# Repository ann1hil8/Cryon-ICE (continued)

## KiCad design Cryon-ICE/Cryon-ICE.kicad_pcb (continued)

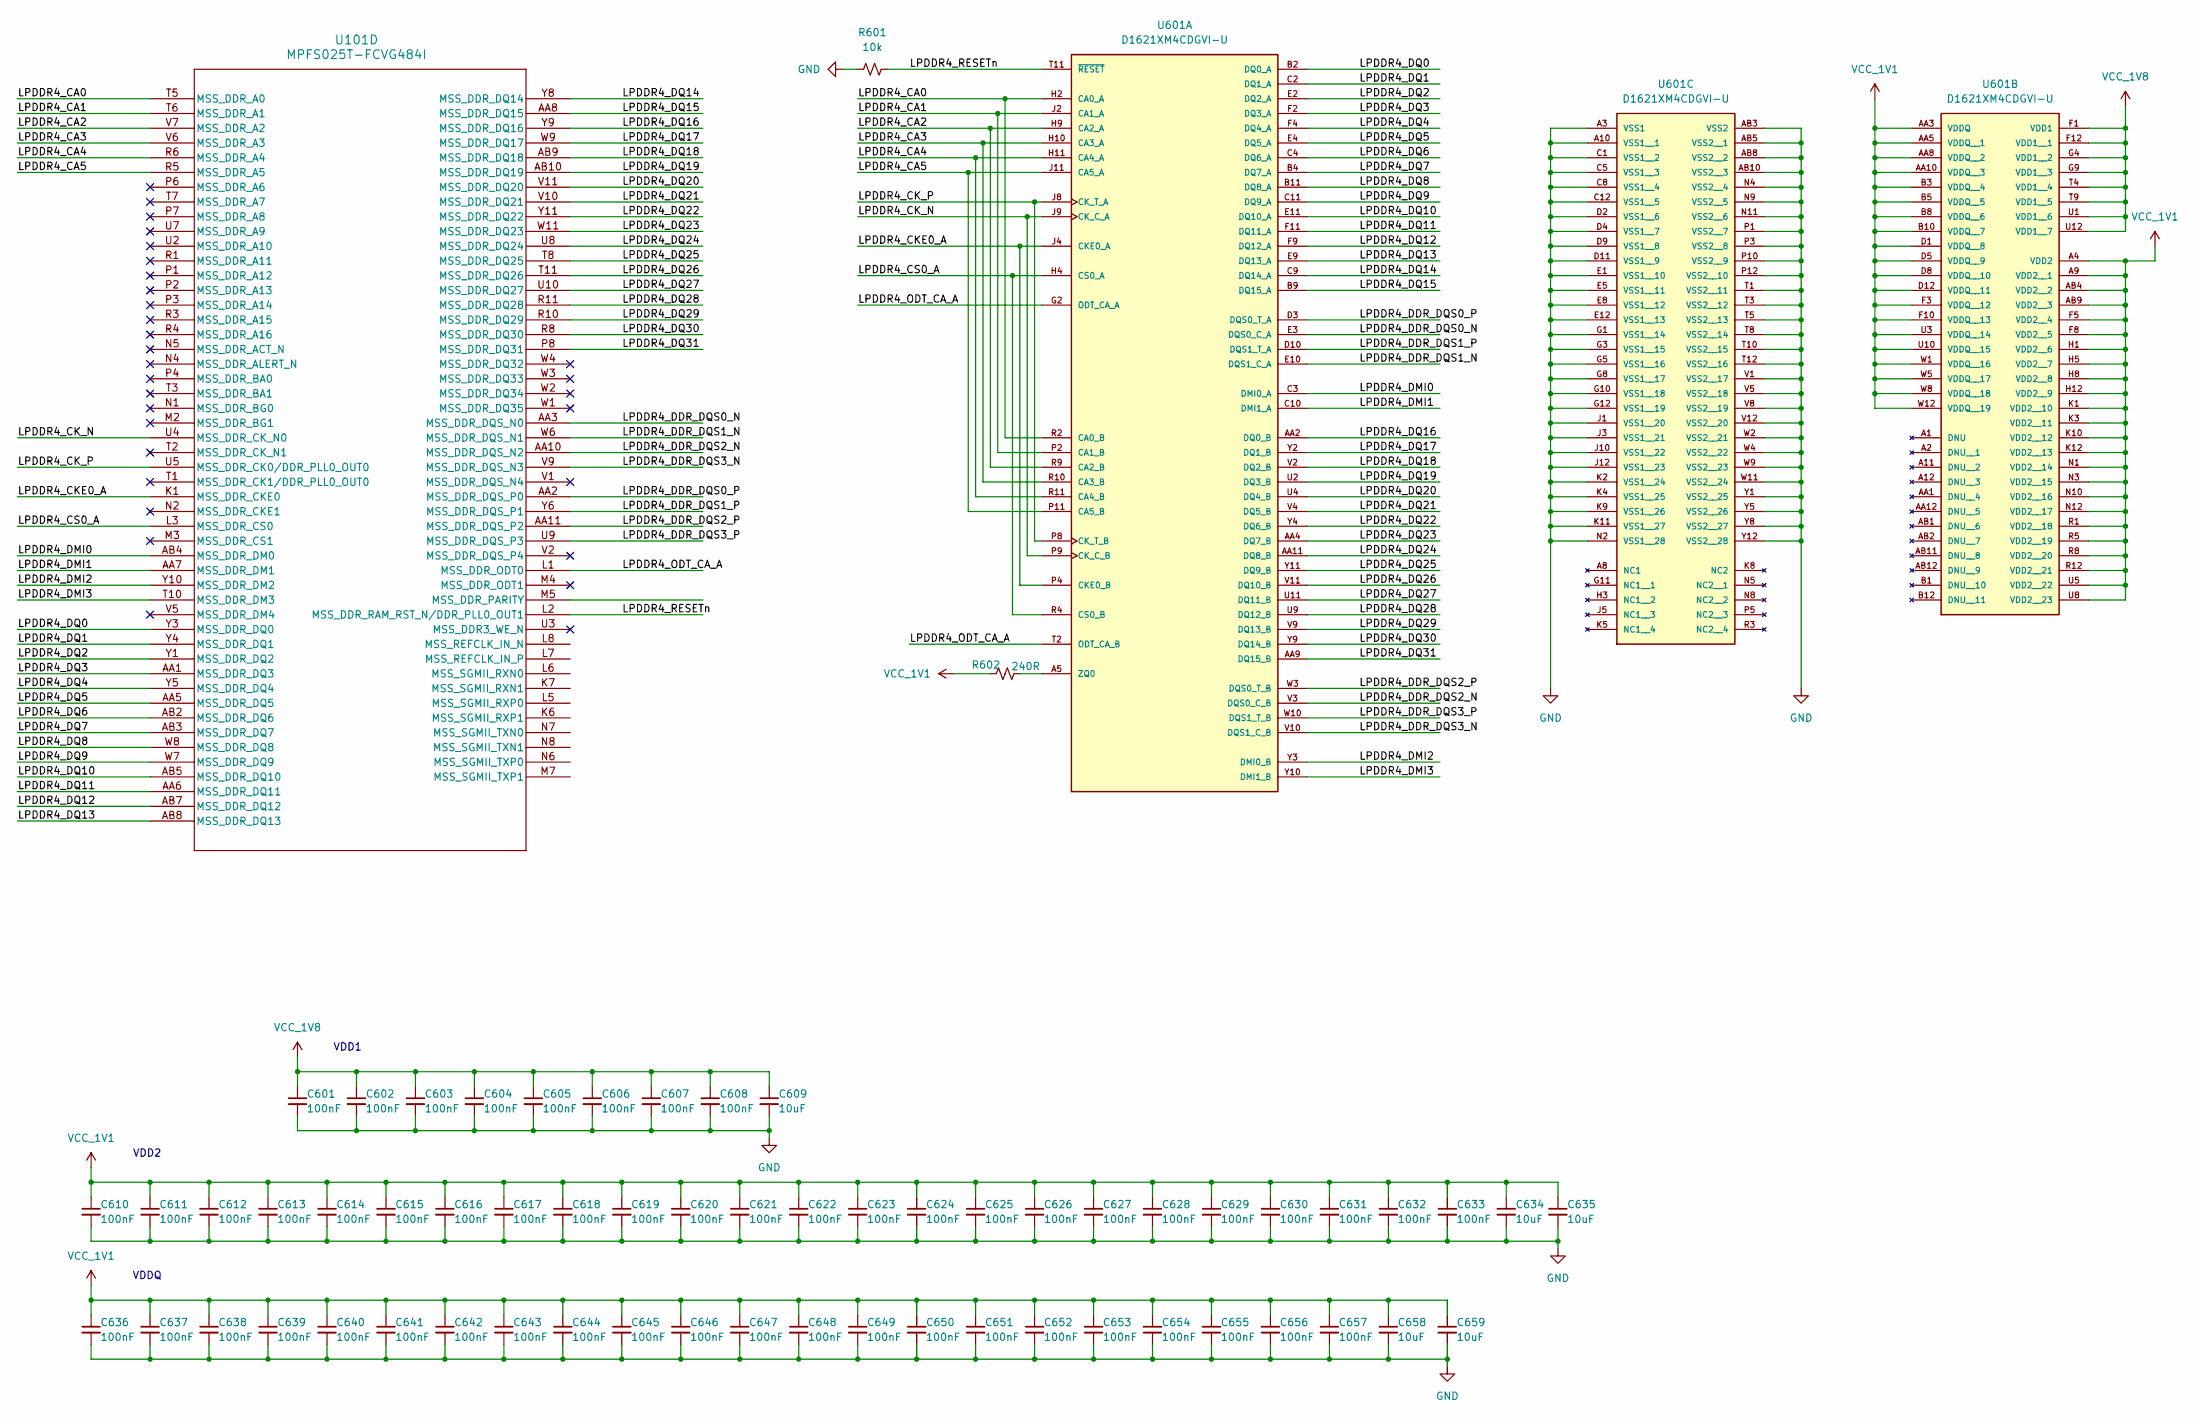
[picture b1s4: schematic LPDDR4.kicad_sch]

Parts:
C601, C602, C603, C604, C605, C606, C607, C608, C610, C611, C612, C613, C614, C615, C616, C617, C618, C619, C620, C621, C622, C623, C624, C625, C626, C627, C628, C629, C630, C631, C632, C633, C636, C637, C638, C639, C640, C641, C642, C643, C644, C645, C646, C647, C648, C649, C650, C651, C652, C653, C654, C655, C656, C657: 100nF; C_0201_0603Metric
C609, C634, C635, C658, C659: 10uF; C_0603_1608Metric
R601: 10k; R_0402_1005Metric
R602: 240R; R_0402_1005Metric
U101: MPFS025T-FCVG484I; MPFS250T&slash_MPFS160T&slash_MPFS095T&slash_MPFS025T-FCVG4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
U601: D1621XM4CDGVI-U; IC_D1621XM4CDGVI-U; PARTREV D00

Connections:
/LPDDR4/LPDDR4_CA0: U101.T5 (MSS_DDR_A0), U601.H2 (CA0_A), U601.R2 (CA0_B)
/LPDDR4/LPDDR4_CA1: U101.T6 (MSS_DDR_A1), U601.J2 (CA1_A), U601.P2 (CA1_B)
/LPDDR4/LPDDR4_CA2: U101.V7 (MSS_DDR_A2), U601.H9 (CA2_A), U601.R9 (CA2_B)
/LPDDR4/LPDDR4_CA3: U101.V6 (MSS_DDR_A3), U601.H10 (CA3_A), U601.R10 (CA3_B)
/LPDDR4/LPDDR4_CA4: U101.R6 (MSS_DDR_A4), U601.H11 (CA4_A), U601.R11 (CA4_B)
/LPDDR4/LPDDR4_CA5: U101.R5 (MSS_DDR_A5), U601.J11 (CA5_A), U601.P11 (CA5_B)
/LPDDR4/LPDDR4_CKE0_A: U101.K1 (MSS_DDR_CKE0), U601.J4 (CKE0_A), U601.P4 (CKE0_B)
/LPDDR4/LPDDR4_CK_N: U101.U4 (MSS_DDR_CK_N0), U601.J9 (CK_C_A), U601.P9 (CK_C_B)
/LPDDR4/LPDDR4_CK_P: U101.U5 (MSS_DDR_CK0/DDR_PLL0_OUT0), U601.J8 (CK_T_A), U601.P8 (CK_T_B)
/LPDDR4/LPDDR4_CS0_A: U101.L3 (MSS_DDR_CS0), U601.H4 (CS0_A), U601.R4 (CS0_B)
/LPDDR4/LPDDR4_DDR_DQS0_N: U101.AA3 (MSS_DDR_DQS_N0), U601.E3 (DQS0_C_A)
/LPDDR4/LPDDR4_DDR_DQS0_P: U101.AA2 (MSS_DDR_DQS_P0), U601.D3 (DQS0_T_A)
/LPDDR4/LPDDR4_DDR_DQS1_N: U101.W6 (MSS_DDR_DQS_N1), U601.E10 (DQS1_C_A)
/LPDDR4/LPDDR4_DDR_DQS1_P: U101.Y6 (MSS_DDR_DQS_P1), U601.D10 (DQS1_T_A)
/LPDDR4/LPDDR4_DDR_DQS2_N: U101.AA10 (MSS_DDR_DQS_N2), U601.V3 (DQS0_C_B)
/LPDDR4/LPDDR4_DDR_DQS2_P: U101.AA11 (MSS_DDR_DQS_P2), U601.W3 (DQS0_T_B)
/LPDDR4/LPDDR4_DDR_DQS3_N: U101.V9 (MSS_DDR_DQS_N3), U601.V10 (DQS1_C_B)
/LPDDR4/LPDDR4_DDR_DQS3_P: U101.U9 (MSS_DDR_DQS_P3), U601.W10 (DQS1_T_B)
/LPDDR4/LPDDR4_DMI0: U101.AB4 (MSS_DDR_DM0), U601.C3 (DMI0_A)
/LPDDR4/LPDDR4_DMI1: U101.AA7 (MSS_DDR_DM1), U601.C10 (DMI1_A)
/LPDDR4/LPDDR4_DMI2: U101.Y10 (MSS_DDR_DM2), U601.Y3 (DMI0_B)
/LPDDR4/LPDDR4_DMI3: U101.T10 (MSS_DDR_DM3), U601.Y10 (DMI1_B)
/LPDDR4/LPDDR4_DQ0: U101.Y3 (MSS_DDR_DQ0), U601.B2 (DQ0_A)
/LPDDR4/LPDDR4_DQ1: U101.Y4 (MSS_DDR_DQ1), U601.C2 (DQ1_A)
/LPDDR4/LPDDR4_DQ2: U101.Y1 (MSS_DDR_DQ2), U601.E2 (DQ2_A)
/LPDDR4/LPDDR4_DQ3: U101.AA1 (MSS_DDR_DQ3), U601.F2 (DQ3_A)
/LPDDR4/LPDDR4_DQ4: U101.Y5 (MSS_DDR_DQ4), U601.F4 (DQ4_A)
/LPDDR4/LPDDR4_DQ5: U101.AA5 (MSS_DDR_DQ5), U601.E4 (DQ5_A)
/LPDDR4/LPDDR4_DQ6: U101.AB2 (MSS_DDR_DQ6), U601.C4 (DQ6_A)
/LPDDR4/LPDDR4_DQ7: U101.AB3 (MSS_DDR_DQ7), U601.B4 (DQ7_A)
/LPDDR4/LPDDR4_DQ8: U101.W8 (MSS_DDR_DQ8), U601.B11 (DQ8_A)
/LPDDR4/LPDDR4_DQ9: U101.W7 (MSS_DDR_DQ9), U601.C11 (DQ9_A)
/LPDDR4/LPDDR4_DQ10: U101.AB5 (MSS_DDR_DQ10), U601.E11 (DQ10_A)
/LPDDR4/LPDDR4_DQ11: U101.AA6 (MSS_DDR_DQ11), U601.F11 (DQ11_A)
/LPDDR4/LPDDR4_DQ12: U101.AB7 (MSS_DDR_DQ12), U601.F9 (DQ12_A)
/LPDDR4/LPDDR4_DQ13: U101.AB8 (MSS_DDR_DQ13), U601.E9 (DQ13_A)
/LPDDR4/LPDDR4_DQ14: U101.Y8 (MSS_DDR_DQ14), U601.C9 (DQ14_A)
/LPDDR4/LPDDR4_DQ15: U101.AA8 (MSS_DDR_DQ15), U601.B9 (DQ15_A)
/LPDDR4/LPDDR4_DQ16: U101.Y9 (MSS_DDR_DQ16), U601.AA2 (DQ0_B)
/LPDDR4/LPDDR4_DQ17: U101.W9 (MSS_DDR_DQ17), U601.Y2 (DQ1_B)
/LPDDR4/LPDDR4_DQ18: U101.AB9 (MSS_DDR_DQ18), U601.V2 (DQ2_B)
/LPDDR4/LPDDR4_DQ19: U101.AB10 (MSS_DDR_DQ19), U601.U2 (DQ3_B)
/LPDDR4/LPDDR4_DQ20: U101.V11 (MSS_DDR_DQ20), U601.U4 (DQ4_B)
/LPDDR4/LPDDR4_DQ21: U101.V10 (MSS_DDR_DQ21), U601.V4 (DQ5_B)
/LPDDR4/LPDDR4_DQ22: U101.Y11 (MSS_DDR_DQ22), U601.Y4 (DQ6_B)
/LPDDR4/LPDDR4_DQ23: U101.W11 (MSS_DDR_DQ23), U601.AA4 (DQ7_B)
/LPDDR4/LPDDR4_DQ24: U101.U8 (MSS_DDR_DQ24), U601.AA11 (DQ8_B)
/LPDDR4/LPDDR4_DQ25: U101.T8 (MSS_DDR_DQ25), U601.Y11 (DQ9_B)
/LPDDR4/LPDDR4_DQ26: U101.T11 (MSS_DDR_DQ26), U601.V11 (DQ10_B)
/LPDDR4/LPDDR4_DQ27: U101.U10 (MSS_DDR_DQ27), U601.U11 (DQ11_B)
/LPDDR4/LPDDR4_DQ28: U101.R11 (MSS_DDR_DQ28), U601.U9 (DQ12_B)
/LPDDR4/LPDDR4_DQ29: U101.R10 (MSS_DDR_DQ29), U601.V9 (DQ13_B)
/LPDDR4/LPDDR4_DQ30: U101.R8 (MSS_DDR_DQ30), U601.Y9 (DQ14_B)
/LPDDR4/LPDDR4_DQ31: U101.P8 (MSS_DDR_DQ31), U601.AA9 (DQ15_B)
/LPDDR4/LPDDR4_ODT_CA_A: U101.L1 (MSS_DDR_ODT0), U601.G2 (ODT_CA_A), U601.T2 (ODT_CA_B)
/LPDDR4/LPDDR4_RESETn: R601.2, U101.L2 (MSS_DDR_RAM_RST_N/DDR_PLL0_OUT1), U601.T11 (~RESET)
GND: C601.2, C602.2, C603.2, C604.2, C605.2, C606.2, C607.2, C608.2, C609.2, C610.2, C611.2, C612.2, C613.2, C614.2, C615.2, C616.2, C617.2, C618.2, C619.2, C620.2, C621.2, C622.2, C623.2, C624.2, C625.2, C626.2, C627.2, C628.2, C629.2, C630.2, C631.2, C632.2, C633.2, C634.2, C635.2, C636.2, C637.2, C638.2, C639.2, C640.2, C641.2, C642.2, C643.2, C644.2, C645.2, C646.2, C647.2, C648.2, C649.2, C650.2, C651.2, C652.2, C653.2, C654.2, C655.2, C656.2, C657.2, C658.2, C659.2, R601.1, U601.A3 (VSS1), U601.A10 (VSS1__1), U601.AB3 (VSS2), U601.AB5 (VSS2__1), U601.AB8 (VSS2__2), U601.AB10 (VSS2__3), U601.C1 (VSS1__2), U601.C5 (VSS1__3), U601.C8 (VSS1__4), U601.C12 (VSS1__5), U601.D2 (VSS1__6), U601.D4 (VSS1__7), U601.D9 (VSS1__8), U601.D11 (VSS1__9), U601.E1 (VSS1__10), U601.E5 (VSS1__11), U601.E8 (VSS1__12), U601.E12 (VSS1__13), U601.G1 (VSS1__14), U601.G3 (VSS1__15), U601.G5 (VSS1__16), U601.G8 (VSS1__17), U601.G10 (VSS1__18), U601.G12 (VSS1__19), U601.J1 (VSS1__20), U601.J3 (VSS1__21), U601.J10 (VSS1__22), U601.J12 (VSS1__23), U601.K2 (VSS1__24), U601.K4 (VSS1__25), U601.K9 (VSS1__26), U601.K11 (VSS1__27), U601.N2 (VSS1__28), U601.N4 (VSS2__4), U601.N9 (VSS2__5), U601.N11 (VSS2__6), U601.P1 (VSS2__7), U601.P3 (VSS2__8), U601.P10 (VSS2__9), U601.P12 (VSS2__10), U601.T1 (VSS2__11), U601.T3 (VSS2__12), U601.T5 (VSS2__13), U601.T8 (VSS2__14), U601.T10 (VSS2__15), U601.T12 (VSS2__16), U601.V1 (VSS2__17), U601.V5 (VSS2__18), U601.V8 (VSS2__19), U601.V12 (VSS2__20), U601.W2 (VSS2__21), U601.W4 (VSS2__22), U601.W9 (VSS2__23), U601.W11 (VSS2__24), U601.Y1 (VSS2__25), U601.Y5 (VSS2__26), U601.Y8 (VSS2__27), U601.Y12 (VSS2__28); also elsewhere on the board
unnamed: R602.2, U601.A5 (ZQ0)
VCC_1V1: C610.1, C611.1, C612.1, C613.1, C614.1, C615.1, C616.1, C617.1, C618.1, C619.1, C620.1, C621.1, C622.1, C623.1, C624.1, C625.1, C626.1, C627.1, C628.1, C629.1, C630.1, C631.1, C632.1, C633.1, C634.1, C635.1, C636.1, C637.1, C638.1, C639.1, C640.1, C641.1, C642.1, C643.1, C644.1, C645.1, C646.1, C647.1, C648.1, C649.1, C650.1, C651.1, C652.1, C653.1, C654.1, C655.1, C656.1, C657.1, C658.1, C659.1, R602.1, U601.A4 (VDD2), U601.A9 (VDD2__1), U601.AA3 (VDDQ), U601.AA5 (VDDQ__1), U601.AA8 (VDDQ__2), U601.AA10 (VDDQ__3), U601.AB4 (VDD2__2), U601.AB9 (VDD2__3), U601.B3 (VDDQ__4), U601.B5 (VDDQ__5), U601.B8 (VDDQ__6), U601.B10 (VDDQ__7), U601.D1 (VDDQ__8), U601.D5 (VDDQ__9), U601.D8 (VDDQ__10), U601.D12 (VDDQ__11), U601.F3 (VDDQ__12), U601.F5 (VDD2__4), U601.F8 (VDD2__5), U601.F10 (VDDQ__13), U601.H1 (VDD2__6), U601.H5 (VDD2__7), U601.H8 (VDD2__8), U601.H12 (VDD2__9), U601.K1 (VDD2__10), U601.K3 (VDD2__11), U601.K10 (VDD2__12), U601.K12 (VDD2__13), U601.N1 (VDD2__14), U601.N3 (VDD2__15), U601.N10 (VDD2__16), U601.N12 (VDD2__17), U601.R1 (VDD2__18), U601.R5 (VDD2__19), U601.R8 (VDD2__20), U601.R12 (VDD2__21), U601.U3 (VDDQ__14), U601.U5 (VDD2__22), U601.U8 (VDD2__23), U601.U10 (VDDQ__15), U601.W1 (VDDQ__16), U601.W5 (VDDQ__17), U601.W8 (VDDQ__18), U601.W12 (VDDQ__19); also elsewhere on the board
VCC_1V8: C601.1, C602.1, C603.1, C604.1, C605.1, C606.1, C607.1, C608.1, C609.1, U601.F1 (VDD1), U601.F12 (VDD1__1), U601.G4 (VDD1__2), U601.G9 (VDD1__3), U601.T4 (VDD1__4), U601.T9 (VDD1__5), U601.U1 (VDD1__6), U601.U12 (VDD1__7); also elsewhere on the board

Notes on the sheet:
VDD2
VDD1
VDDQ

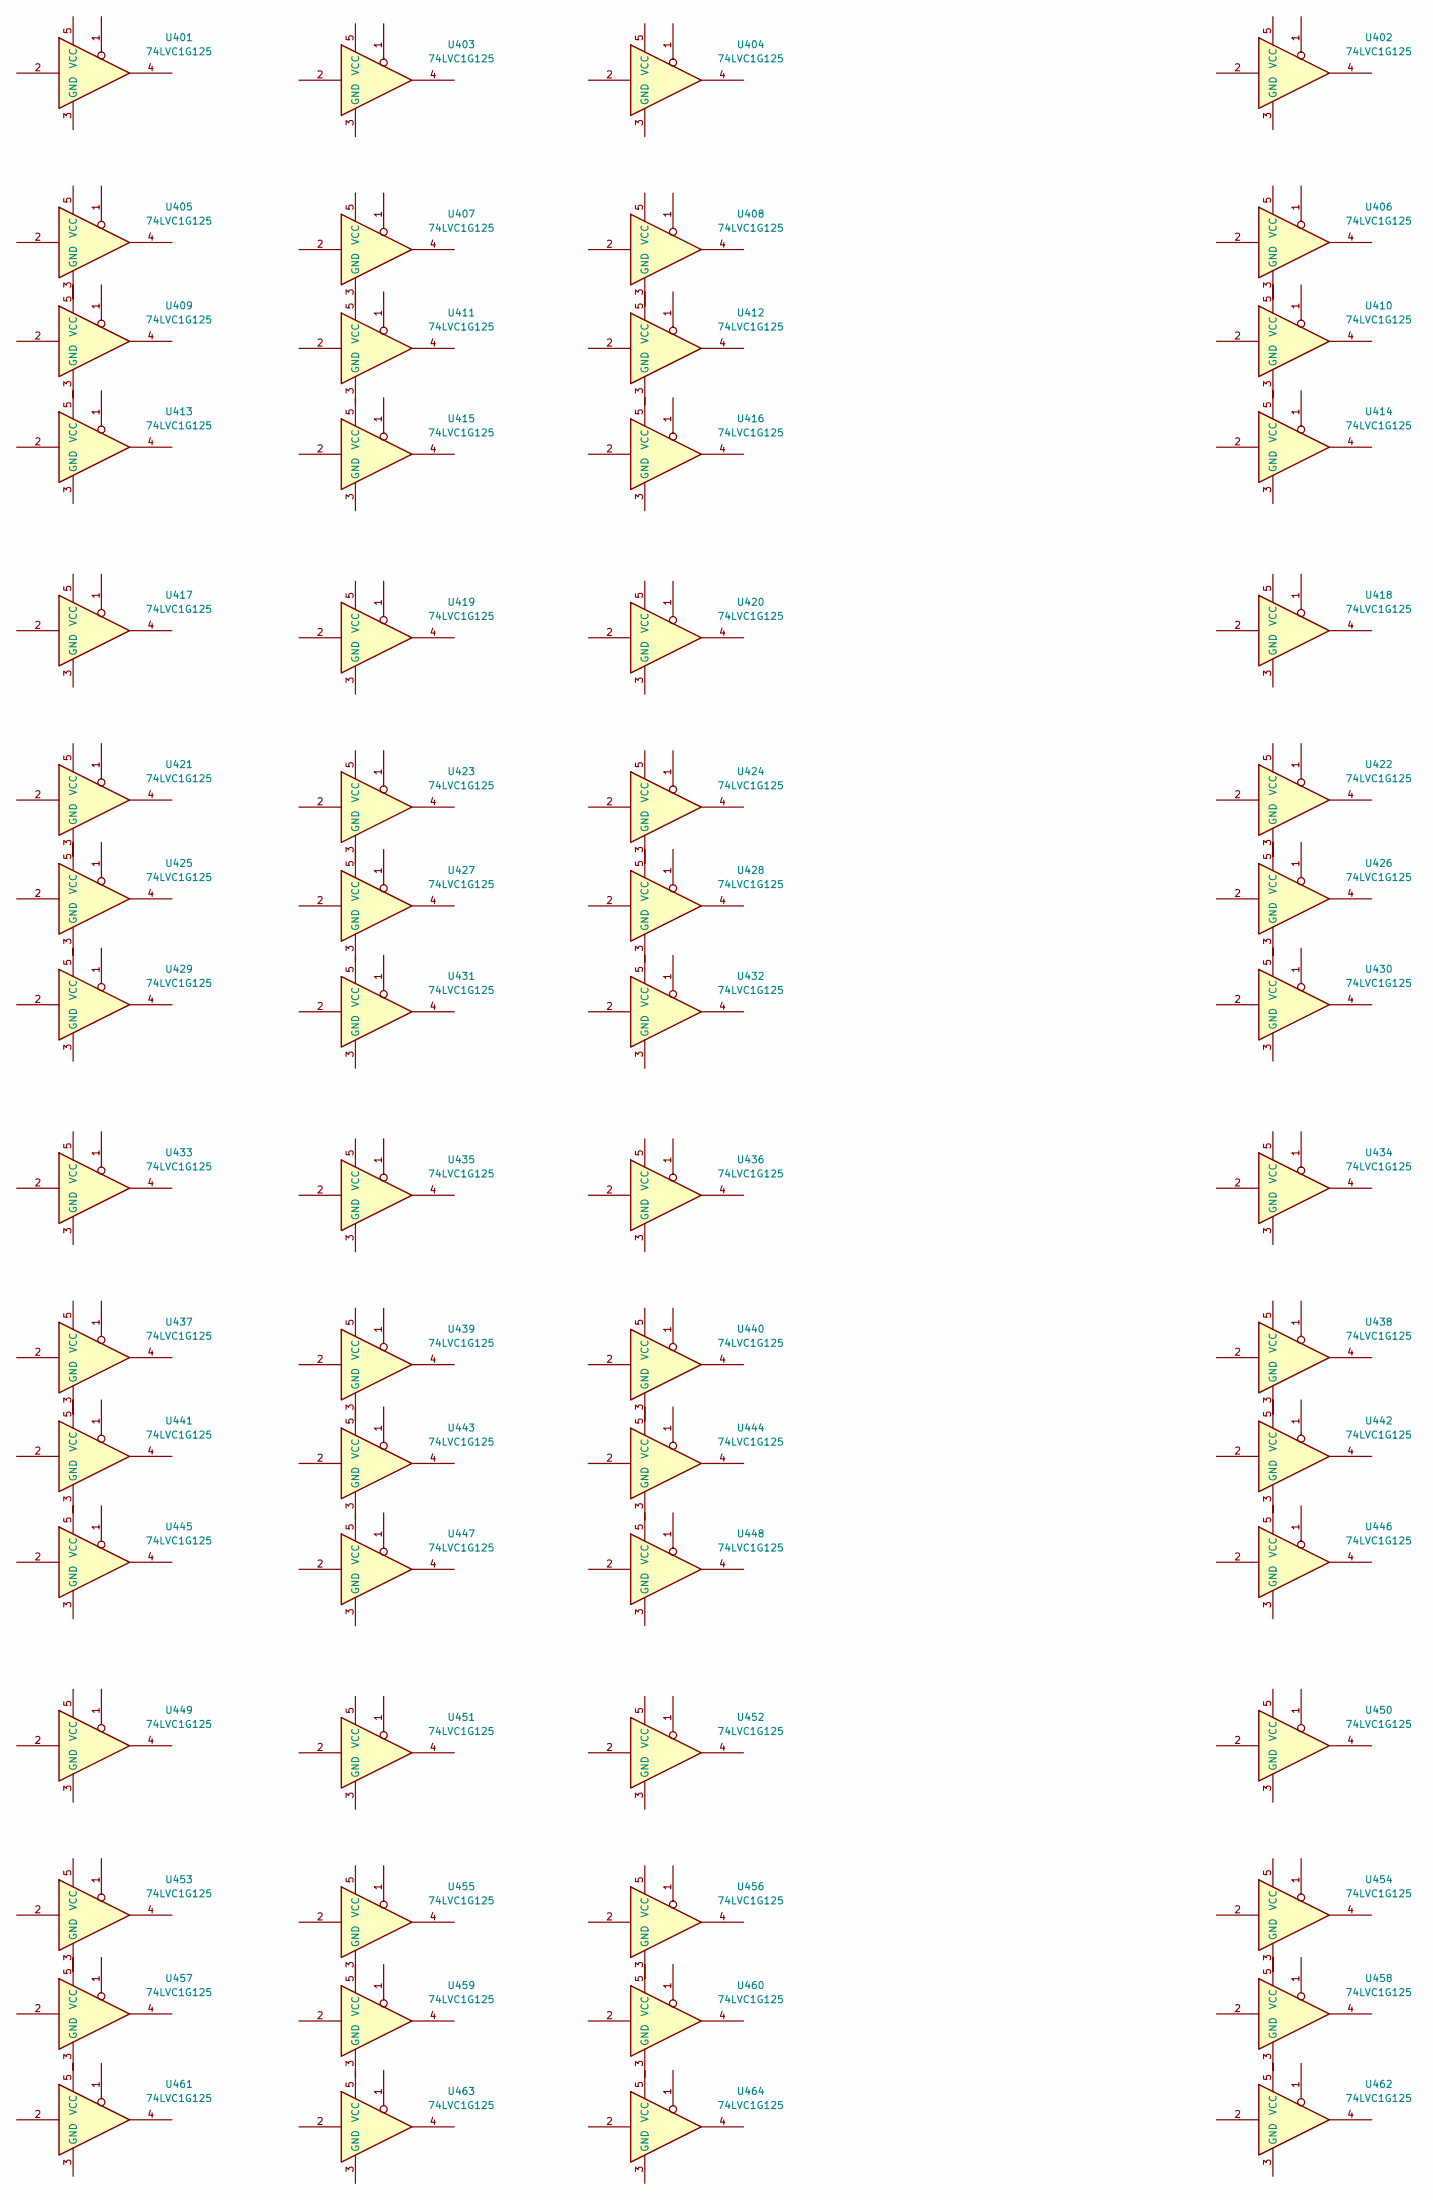
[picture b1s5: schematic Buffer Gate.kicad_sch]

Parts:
U401, U402, U403, U404, U405, U406, U407, U408, U409, U410, U411, U412, U413, U414, U415, U416, U417, U418, U419, U420, U421, U422, U423, U424, U425, U426, U427, U428, U429, U430, U431, U432, U433, U434, U435, U436, U437, U438, U439, U440, U441, U442, U443, U444, U445, U446, U447, U448, U449, U450, U451, U452, U453, U454, U455, U456, U457, U458, U459, U460, U461, U462, U463, U464: 74LVC1G125; DSF6_TEX

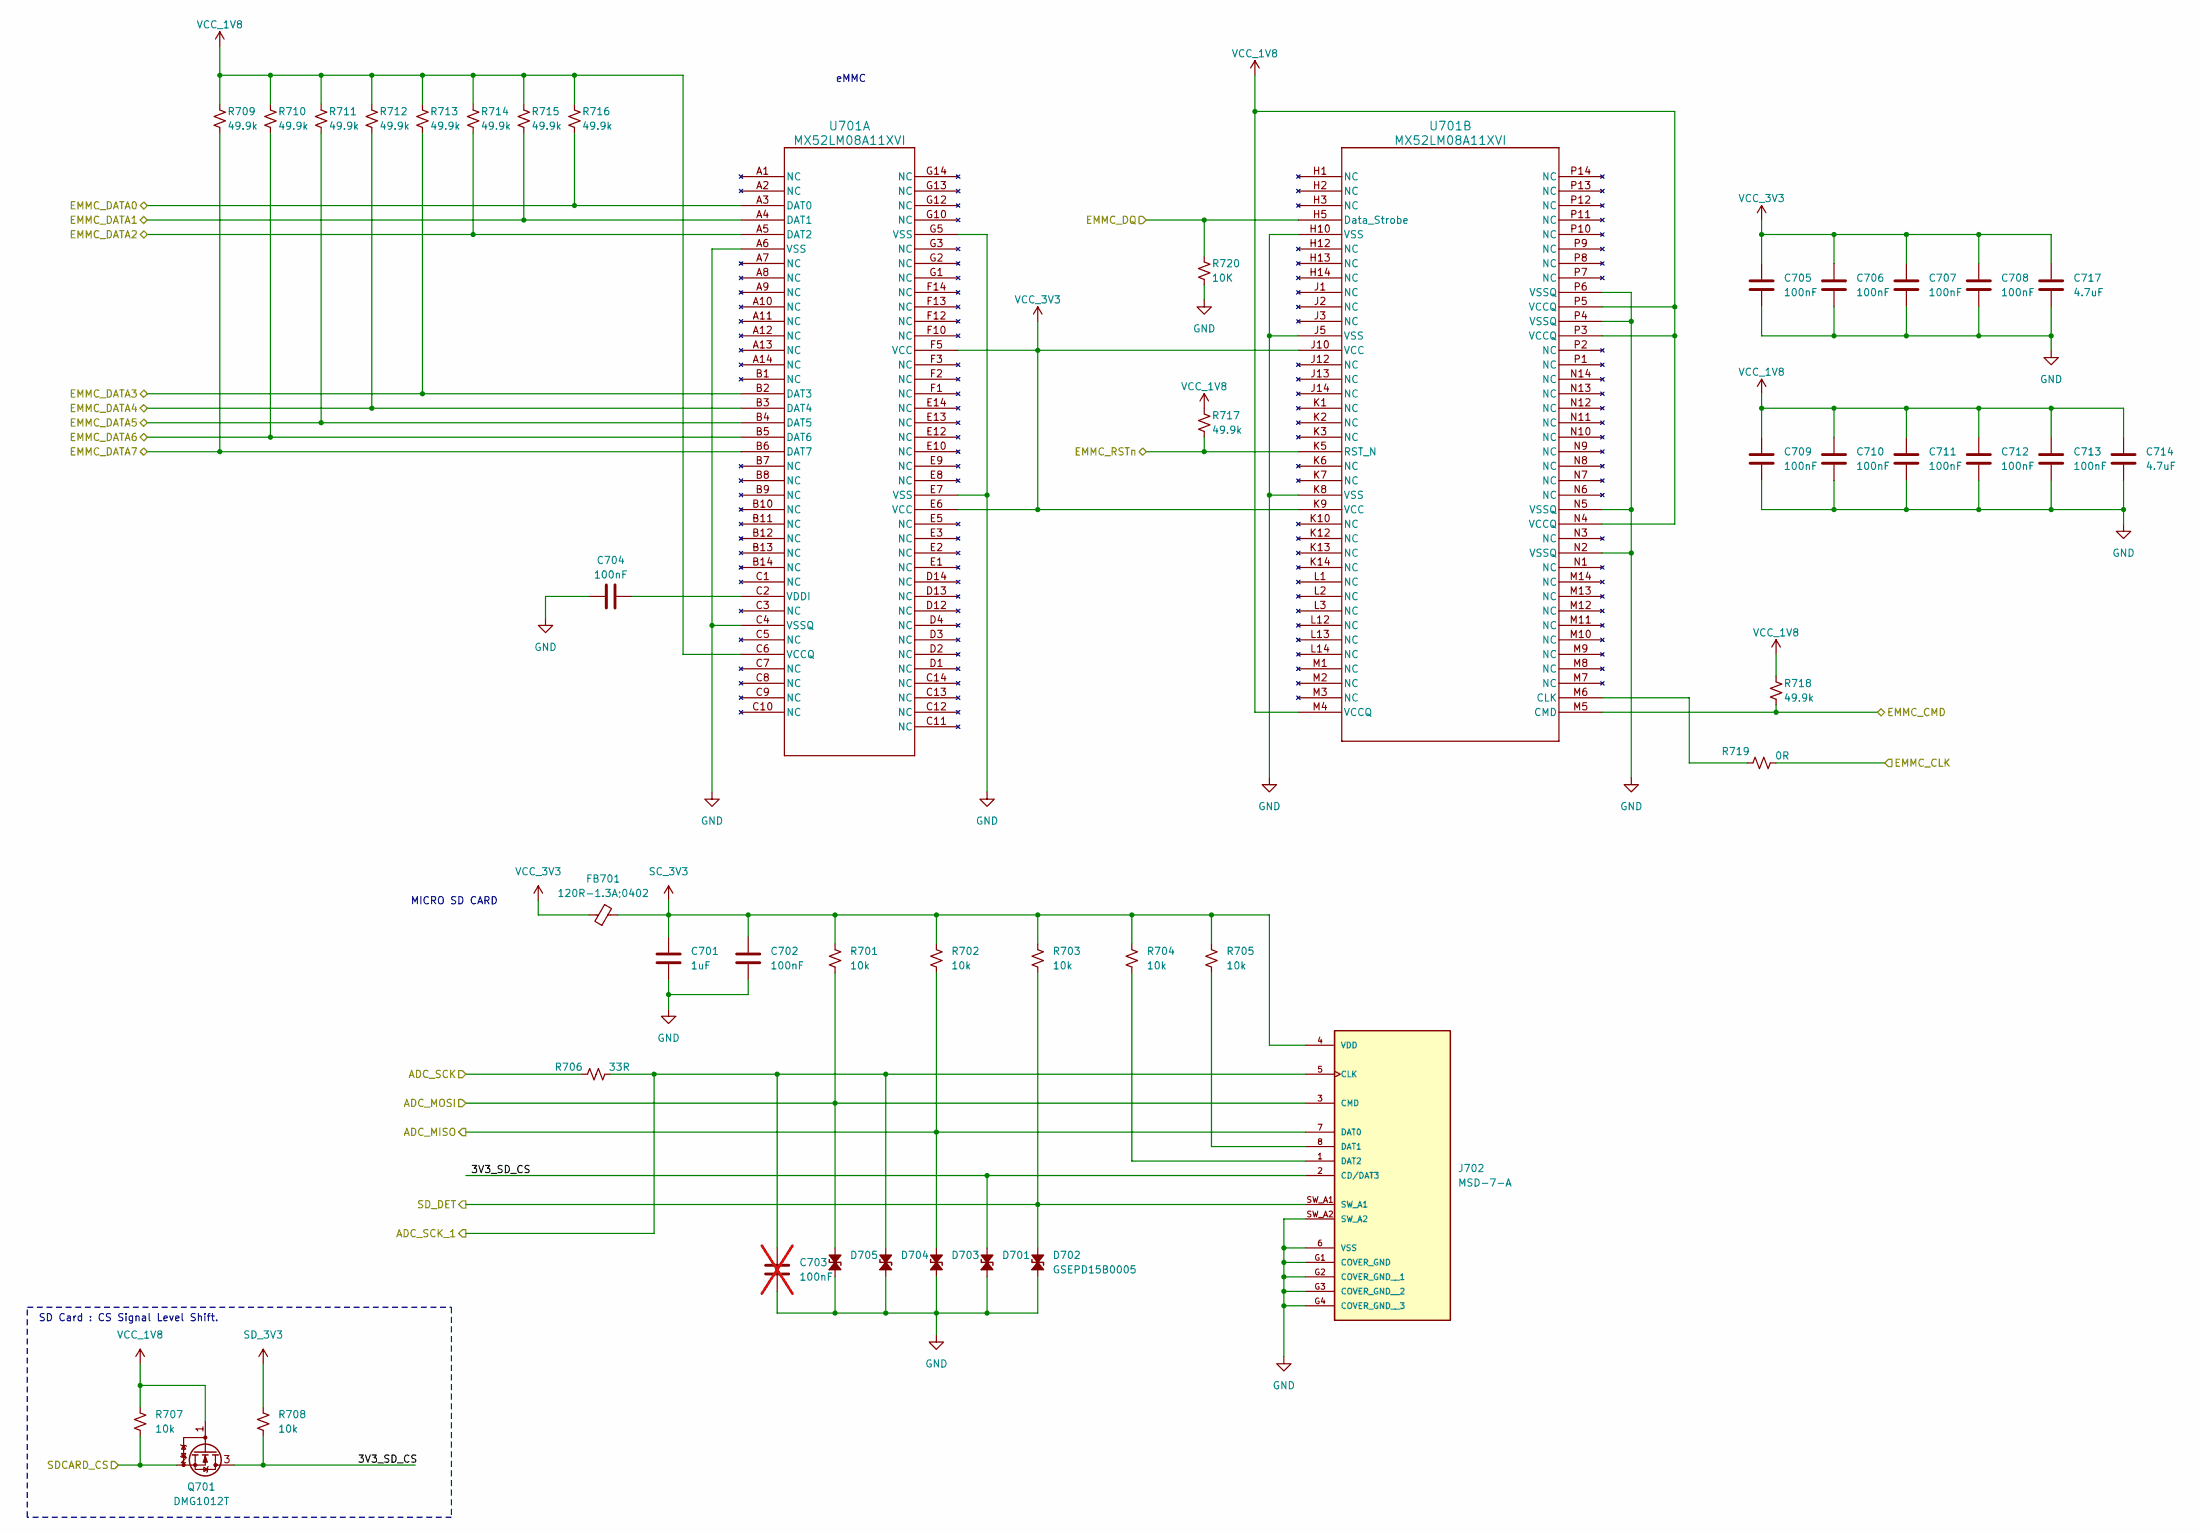
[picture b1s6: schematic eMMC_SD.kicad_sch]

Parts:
C701: 1uF; C_0402_1005Metric
C702, C704, C705, C706, C707, C708, C709, C710, C711, C712, C713: 100nF; C_0402_1005Metric
C703: 100nF; C_0402_1005Metric; not fitted
C714, C717: 4.7uF; C_0201_0603Metric
D701, D702, D703, D704, D705: GSEPD15B0005; D_GSEPD15B0005_01005_0402Metric
FB701: 120R-1.3A;0402; BLM15P_FBD
J702: MSD-7-A; CUI_MSD-7-A; PARTREV 1.0
Q701: DMG1012T; DMG1012-SOT-523
R701, R702, R703, R704, R705, R707, R708: 10k; R_0402_1005Metric
R706: 33R; R_0402_1005Metric
R709, R710, R711, R712, R713, R714, R715, R716, R717, R718: 49.9k; R_0402_1005Metric
R719: 0R; R_0402_1005Metric
R720: 10K; R_0402_1005Metric
U701: MX52LM08A11XVI; 153BGA_11p5x13x1_MAC

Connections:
/SD_DET: D702.2 (A2), J702.SW_A1, R703.2; also elsewhere on the board
/eMMC_SD/3V3_SD_CS: D701.2 (A2), J702.2 (CD/DAT3), Q701.3 (D), R708.2
/eMMC_SD/ADC_MISO: D703.2 (A2), J702.7 (DAT0), R702.2; also elsewhere on the board
/eMMC_SD/ADC_MOSI: D705.2 (A2), J702.3 (CMD), R701.2; also elsewhere on the board
/eMMC_SD/ADC_SCK: R706.1; also elsewhere on the board
/eMMC_SD/ADC_SCK_1: C703.1, D704.2 (A2), J702.5 (CLK), R706.2
/eMMC_SD/EMMC_CLK: R719.2; also elsewhere on the board
/eMMC_SD/EMMC_CMD: R718.2, U701.M5 (CMD); also elsewhere on the board
/eMMC_SD/EMMC_DATA0: R716.2, U701.A3 (DAT0); also elsewhere on the board
/eMMC_SD/EMMC_DATA1: R715.2, U701.A4 (DAT1); also elsewhere on the board
/eMMC_SD/EMMC_DATA2: R714.2, U701.A5 (DAT2); also elsewhere on the board
/eMMC_SD/EMMC_DATA3: R713.2, U701.B2 (DAT3); also elsewhere on the board
/eMMC_SD/EMMC_DATA4: R712.2, U701.B3 (DAT4); also elsewhere on the board
/eMMC_SD/EMMC_DATA5: R711.2, U701.B4 (DAT5); also elsewhere on the board
/eMMC_SD/EMMC_DATA6: R710.2, U701.B5 (DAT6); also elsewhere on the board
/eMMC_SD/EMMC_DATA7: R709.2, U701.B6 (DAT7); also elsewhere on the board
/eMMC_SD/EMMC_DQ: R720.1, U701.H5 (Data_Strobe); also elsewhere on the board
/eMMC_SD/EMMC_RSTn: R717.2, U701.K5 (RST_N); also elsewhere on the board
/eMMC_SD/SDCARD_CS: Q701.2 (S), R707.2; also elsewhere on the board
GND: C701.2, C702.2, C703.2, C704.1, C705.1, C706.1, C707.1, C708.1, C709.1, C710.1, C711.1, C712.1, C713.1, C714.1, C717.1, D701.1 (A1), D702.1 (A1), D703.1 (A1), D704.1 (A1), D705.1 (A1), J702.6 (VSS), J702.G1 (COVER_GND), J702.G2 (COVER_GND__1), J702.G3 (COVER_GND__2), J702.G4 (COVER_GND__3), J702.SW_A2, R720.2, U701.A6 (VSS), U701.C4 (VSSQ), U701.E7 (VSS), U701.G5 (VSS), U701.H10 (VSS), U701.J5 (VSS), U701.K8 (VSS), U701.N2 (VSSQ), U701.N5 (VSSQ), U701.P4 (VSSQ), U701.P6 (VSSQ); also elsewhere on the board
unnamed: J702.8 (DAT1), R705.2
unnamed: J702.1 (DAT2), R704.2
unnamed: C704.2, U701.C2 (VDDI)
unnamed: R719.1, U701.M6 (CLK)
SC_3V3: C701.1, C702.1, FB701.2, J702.4 (VDD), R701.1, R702.1, R703.1, R704.1, R705.1
SD_3V3: R708.1
VCC_1V8: C709.2, C710.2, C711.2, C712.2, C713.2, C714.2, Q701.1 (G), R707.1, R709.1, R710.1, R711.1, R712.1, R713.1, R714.1, R715.1, R716.1, R717.1, R718.1, U701.C6 (VCCQ), U701.M4 (VCCQ), U701.N4 (VCCQ), U701.P3 (VCCQ), U701.P5 (VCCQ); also elsewhere on the board
VCC_3V3: C705.2, C706.2, C707.2, C708.2, C717.2, FB701.1, U701.E6 (VCC), U701.F5 (VCC), U701.J10 (VCC), U701.K9 (VCC); also elsewhere on the board

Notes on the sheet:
SD Card : CS Signal Level Shift.
eMMC
MICRO SD CARD

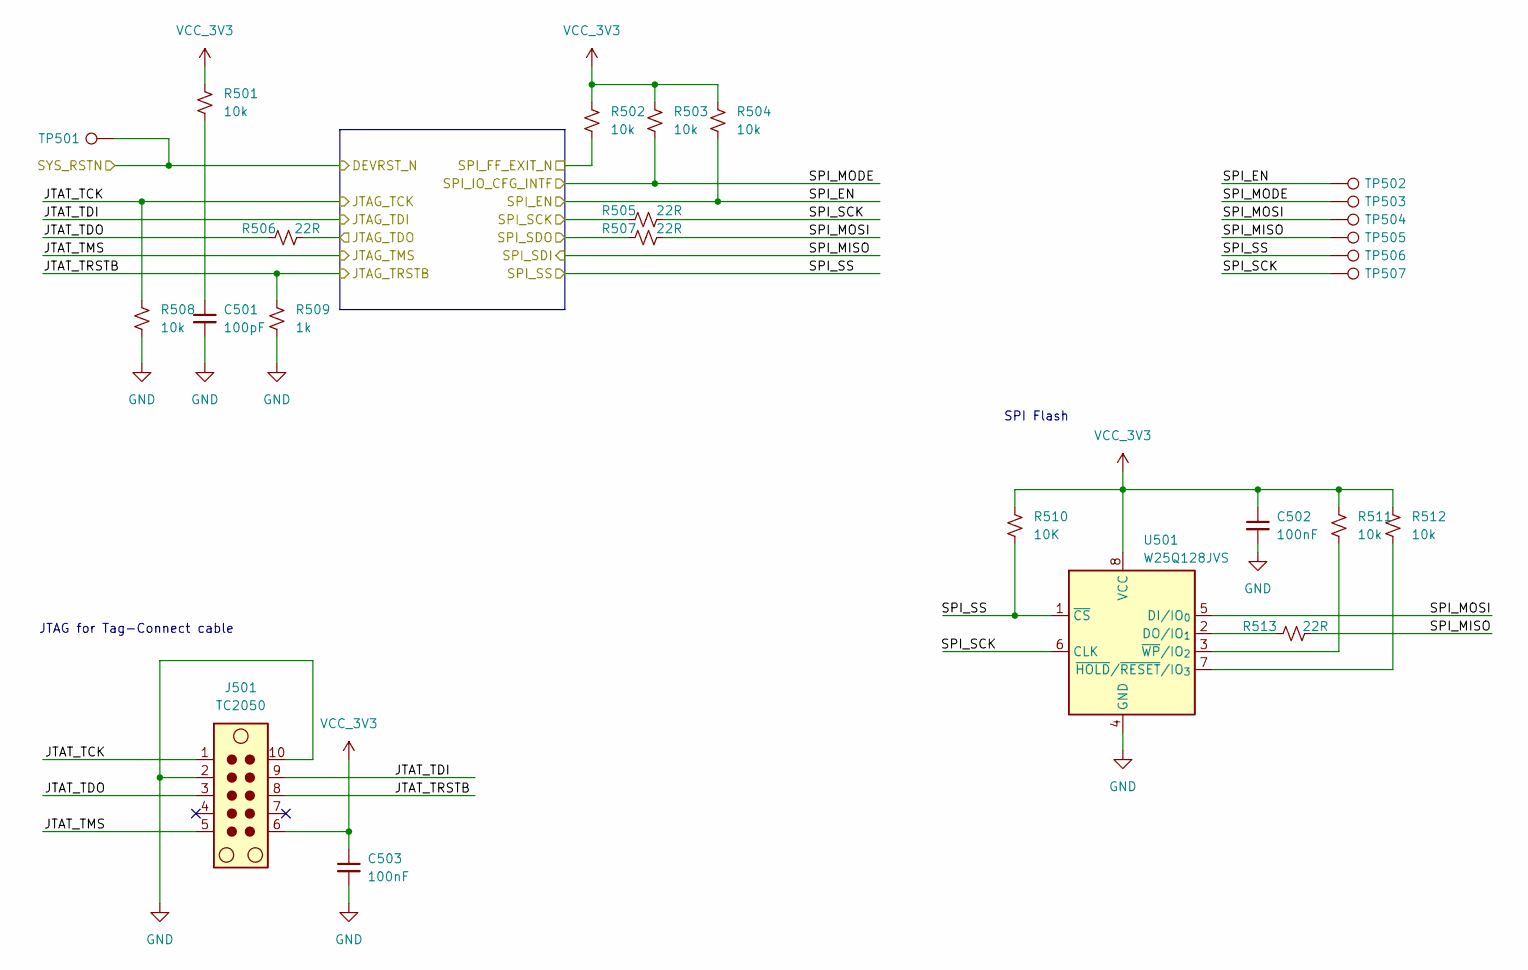
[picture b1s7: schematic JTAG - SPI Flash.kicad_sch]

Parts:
C501: 100pF; C_0402_1005Metric
C502, C503: 100nF; C_0402_1005Metric
J501: TC2050; Tag-Connect_TC2050-IDC-NL_2x05_P1.27mm_Vertical
R501, R502, R503, R504, R508, R511, R512: 10k; R_0402_1005Metric
R505, R506, R507, R513: 22R; R_0402_1005Metric
R509: 1k; R_0402_1005Metric
R510: 10K; R_0402_1005Metric
TP501, TP502, TP503, TP504, TP505, TP506, TP507: TestPoint; TestPoint_Pad_D1.0mm
U501: W25Q128JVS; SOIC-8_5.3x5.3mm_P1.27mm

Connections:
/JTAG - SPI Flash/DEVRST_N: TP501.1 (1_1); also elsewhere on the board
/JTAG - SPI Flash/JTAG_TDO: R506.2; also elsewhere on the board
/JTAG - SPI Flash/JTAT_TCK: J501.1, R508.1; also elsewhere on the board
/JTAG - SPI Flash/JTAT_TDI: J501.9; also elsewhere on the board
/JTAG - SPI Flash/JTAT_TDO: J501.3, R506.1
/JTAG - SPI Flash/JTAT_TMS: J501.5; also elsewhere on the board
/JTAG - SPI Flash/JTAT_TRSTB: J501.8, R509.1; also elsewhere on the board
/JTAG - SPI Flash/SPI_EN: R504.2, TP502.1 (1_1); also elsewhere on the board
/JTAG - SPI Flash/SPI_FF_EXIT_N: R502.2; also elsewhere on the board
/JTAG - SPI Flash/SPI_MISO: R513.2, TP505.1 (1_1); also elsewhere on the board
/JTAG - SPI Flash/SPI_MODE: R503.2, TP503.1 (1_1); also elsewhere on the board
/JTAG - SPI Flash/SPI_MOSI: R507.2, TP504.1 (1_1), U501.5 (DI/IO_{0})
/JTAG - SPI Flash/SPI_SCK: R505.1, R505.2, TP507.1 (1_1), U501.6 (CLK); also elsewhere on the board
/JTAG - SPI Flash/SPI_SDO: R507.1; also elsewhere on the board
/JTAG - SPI Flash/SPI_SS: R510.2, TP506.1 (1_1), U501.1 (~CS); also elsewhere on the board
GND: C501.2, C502.2, C503.2, J501.2, J501.10, R508.2, R509.2, U501.4 (GND); also elsewhere on the board
unnamed: C501.1, R501.2
unnamed: R513.1, U501.2 (DO/IO_{1})
unnamed: R512.2, U501.7 (~HOLD/~RESET/IO_{3})
unnamed: R511.2, U501.3 (~WP/IO_{2})
VCC_3V3: C502.1, C503.1, J501.6, R501.1, R502.1, R503.1, R504.1, R510.1, R511.1, R512.1, U501.8 (VCC); also elsewhere on the board

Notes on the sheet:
SPI Flash
JTAG for Tag-Connect cable

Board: 4 copper layers, 251 parts (0 on the bottom side), 150 nets, no tracks yet.

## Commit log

2026-06-16 Initial commit of Cryon-ICE project and component library
2026-06-16 Updated .gitignore
2026-06-16 Batch converted all 3D model absolute paths to relative
2026-06-16 Updated netlist connection rules
2026-06-17 Added micro-sd to schematic
2026-06-17 Added eMMC
